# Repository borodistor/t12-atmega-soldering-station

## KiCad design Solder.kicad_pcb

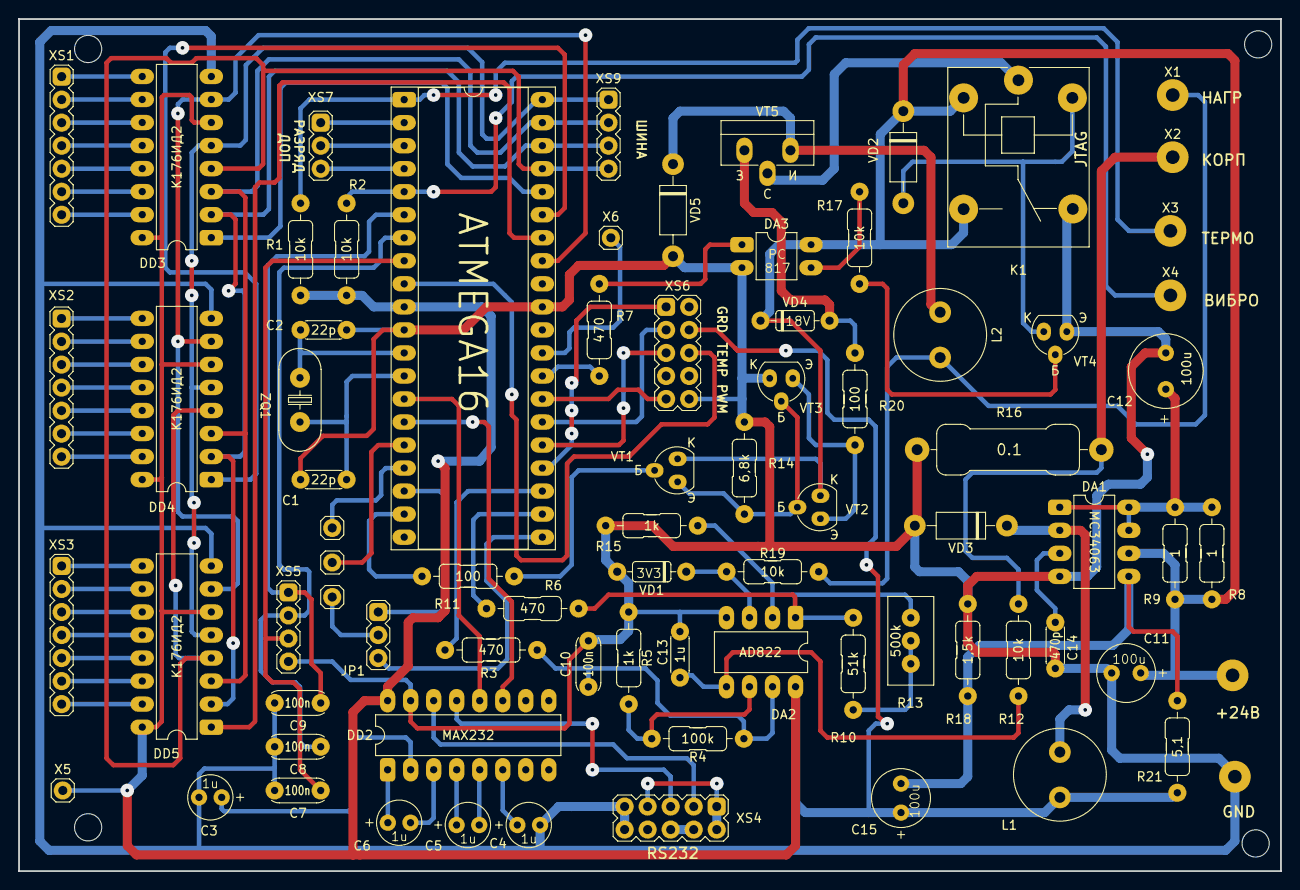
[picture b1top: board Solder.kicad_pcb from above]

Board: 2 copper layers, 139.2 x 94.0 mm, 78 parts (0 on the bottom side), 92 nets.

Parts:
C1, C2: 22p; 22pf
C3, C4, C5, C6: 1u; 1uf 50V
C7, C8, C9, C10: 100n
C11, C15: 100u; 100uf 16V
C12: 100u; 100uf 50V
C13: 1u
C14: 470p; 470pf
DA1: MC34063; MC34063-DIP
DA2: AD822; AD822-DIP
DA3: PC817; PC817-DIP
DD1: ATmega16A; AtMega16-DIP-S
DD2: MAX232; MAX232-DIP
DD3, DD4, DD5: К176ИД2
JP1: 1x03F; 1x03
K1: SRD-24VDC-SL-C
L1, L2: 100uH; 100uH Neosid
R1, R2, R12, R17, R19: 10k; 10K
R3, R6, R7: 470; 470R
R4: 100k; 100K
R5, R15: 1k; 1K
R8, R9: 1; 1R
R10: 51k; 51K
R11, R20: 100; 100R
R13: 500k; 3296W 500k
R14: 6,8k; 6K8
R16: 0.1; 0.1R
R18: 1,5k; 1R
R21: 5,1; 5K1
VD1: 1N4728
VD2: 1N4004; FR107
VD3: 1N5819
VD4: 1N4746
VD5: FR107
VT1: BC548
VT2, VT4: BC547
VT3: BC557
VT5: IRFZ44
X1: НАГРЕВ; PIN-Wire
X2: ТОКОСЪЁМ; PIN-Wire
X3: ТЕРМО; PIN-Wire
X4: ВИБРО; PIN-Wire
X5, X6, X7, X8, X9: 1x01; Pin
X10: ПИТАНИЕ; PIN-Wire
X11: КОРПУС; PIN-Wire
XS1, XS2, XS3: 1x07
XS4: RS232; 2x05
XS5: 1x04F; 1x04
XS6: JTAG; 2x05
XS7: ДОП РАЗРЯД; 1x03
XS9: ЦИФ ШИНА; 1x04
ZQ1: 16 МГц; ECS-H

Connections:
+5V: C15.1, DA2.8 (V+), DD1.10 (VCC), DD2.16 (VCC), DD3.6 (M), DD3.16 (VCC), DD4.6 (M), DD4.16 (VCC), DD5.6 (M), DD5.16 (VCC), L1.1, R1.2, R2.2, R21.2, X5.1, XS6.4
+24V: C11.1, DA1.6 (Vin), DA3.4, K1.2, K1.3, R8.2, R9.2, VD2.1 (K), VD4.1 (K), VT1.C (К), VT2.C (К), X10.1
/BLK: DD1.33 (PA7), DD3.7 (K), DD4.7 (K), DD5.7 (K)
/CURRENT: DD1.23 (PC1), R3.1
/D0: DD1.40 (PA0), DD3.5 (D0), DD4.5 (D0), DD5.5 (D0), XS9.1
/D1: DD1.39 (PA1), DD3.3 (D1), DD4.3 (D1), DD5.3 (D1), XS9.2
/D2: DD1.38 (PA2), DD3.2 (D2), DD4.2 (D2), DD5.2 (D2), XS9.3
/D3: DD1.37 (PA3), DD3.4 (D3), DD4.4 (D3), DD5.4 (D3), XS9.4
/GUARD: DD1.28 (PC6), R7.1
/GUARD1: DD1.17 (PD3), X9.1
/PWM: DD1.19 (PD5), R11.1
/PWM1: JP1.2, X7.1
/RST: DD1.9 (~RESET), XS6.6
/RX: DD1.14 (PD0), DD2.12 (R1OUT)
/S0: DD1.36 (PA4), DD3.1 (S)
/S1: DD1.35 (PA5), DD4.1 (S)
/S2: DD1.34 (PA6), DD5.1 (S)
/SA0: DD1.2 (PB1), XS7.1
/SA1: DD1.3 (PB2), XS7.2
/SA2: DD1.4 (PB3), XS7.3
/TCK: DD1.24 (PC2), XS6.1
/TDI: DD1.27 (PC5), XS6.9
/TDO: DD1.26 (PC4), XS6.3
/TEMP: DD1.22 (PC0), R6.1
/TEMP1: DD1.16 (PD2), X8.1
/TMS: DD1.25 (PC3), XS6.5
/TX: DD1.15 (PD1), DD2.11 (T1IN)
GND: C1.1, C2.1, C3.2, C4.2, C7.2, C8.2, C9.2, C10.2, C11.2, C12.2, C13.2, C14.2, DA1.4 (GND), DA2.4 (V-), DA3.2, DD1.11 (GND), DD1.31 (GND), DD2.15 (GND), DD3.8 (GND), DD4.8 (GND), DD5.8 (GND), K1.4, R5.1, R14.1, R15.1, R16.1, R18.1, VD1.2 (A), VD3.2 (A), VD5.2 (A), VT3.C (К), VT4.E (Э), X11.1, XS4.9, XS4.10, XS5.4, XS6.10
unnamed: C10.1, DA2.7, R3.2, R4.1
unnamed: C12.1, DA1.1 (SwC), DA1.7 (Ipk), DA1.8 (DC), R8.1, R9.1
unnamed: DA1.2 (SwE), L1.2, VD3.1 (K)
unnamed: C14.1, DA1.3 (TC)
unnamed: C15.2, DA1.5 (Vfb), R18.2, R21.1
unnamed: DA2.1, R6.2, R10.2
unnamed: DA2.3 (+), R19.1, VD1.1 (K)
unnamed: DA2.2 (-), R13.3, R15.2
unnamed: C13.1, DA2.5 (+), R12.1
unnamed: DA2.6 (-), R4.2, R5.2
unnamed: DA3.1, R7.2
unnamed: DA3.3, R17.1
unnamed: DD1.1 (PB0), R1.1, X3.1
unnamed: DD1.5 (PB4), R2.1, X4.1
unnamed: C9.1, DD1.6 (PB5), XS5.1
unnamed: C8.1, DD1.7 (PB6), XS5.2
unnamed: C7.1, DD1.8 (PB7), XS5.3
unnamed: DD1.29 (PC7), X6.1
unnamed: DD1.18 (PD4), JP1.1
unnamed: DD1.21 (PD7), JP1.3
unnamed: C1.2, DD1.13 (XTAL1), ZQ1.2
unnamed: C2.2, DD1.12 (XTAL2), ZQ1.1
unnamed: C6.1, DD2.1 (C1+)
unnamed: C6.2, DD2.3 (C1-)
unnamed: C5.1, DD2.4 (C2+)
unnamed: C5.2, DD2.5 (C2-)
unnamed: DD2.13 (R1IN), XS4.5
unnamed: DD2.14 (T1OUT), XS4.3
unnamed: C3.1, DD2.2 (VS+)
unnamed: C4.1, DD2.6 (VS-)
unnamed: DD3.9 (A), XS1.1
unnamed: DD3.10 (B), XS1.2
unnamed: DD3.11 (C), XS1.3
unnamed: DD3.12 (D), XS1.4
unnamed: DD3.13 (E), XS1.5
unnamed: DD3.14 (F), XS1.6
unnamed: DD3.15 (G), XS1.7
unnamed: DD4.9 (A), XS2.1
unnamed: DD4.10 (B), XS2.2
unnamed: DD4.11 (C), XS2.3
unnamed: DD4.12 (D), XS2.4
unnamed: DD4.13 (E), XS2.5
unnamed: DD4.14 (F), XS2.6
unnamed: DD4.15 (G), XS2.7
unnamed: DD5.9 (A), XS3.1
unnamed: DD5.10 (B), XS3.2
unnamed: DD5.11 (C), XS3.3
unnamed: DD5.12 (D), XS3.4
unnamed: DD5.13 (E), XS3.5
unnamed: DD5.14 (F), XS3.6
unnamed: DD5.15 (G), XS3.7
unnamed: K1.1, VT5.D
unnamed: R10.1, R13.1, R13.2
unnamed: K1.5, VD2.2 (A), VT4.C (К)
unnamed: R20.2, VD4.2 (A), VT5.G
unnamed: L2.1, VD5.1 (K), VT5.S
unnamed: R11.2, VT1.B (Б)
unnamed: R14.2, VT1.E (Э), VT2.B (Б), VT3.B (Б)
unnamed: R20.1, VT2.E (Э), VT3.E (Э)
unnamed: R17.2, VT4.B (Б)
unnamed: L2.2, R19.2, X1.1
unnamed: R12.2, R16.2, X2.1
unnamed: XS4.1, XS4.2, XS4.7
unnamed: XS4.4, XS4.6

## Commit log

2023-08-28 Fixed schematic errors
2023-08-28 Updated schematic picture
2023-08-29 Routed board
2023-08-29 Fixed board captions
